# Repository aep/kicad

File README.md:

my personal collection of kicad components.
Some are not verified.

consider the ones i made public domain.

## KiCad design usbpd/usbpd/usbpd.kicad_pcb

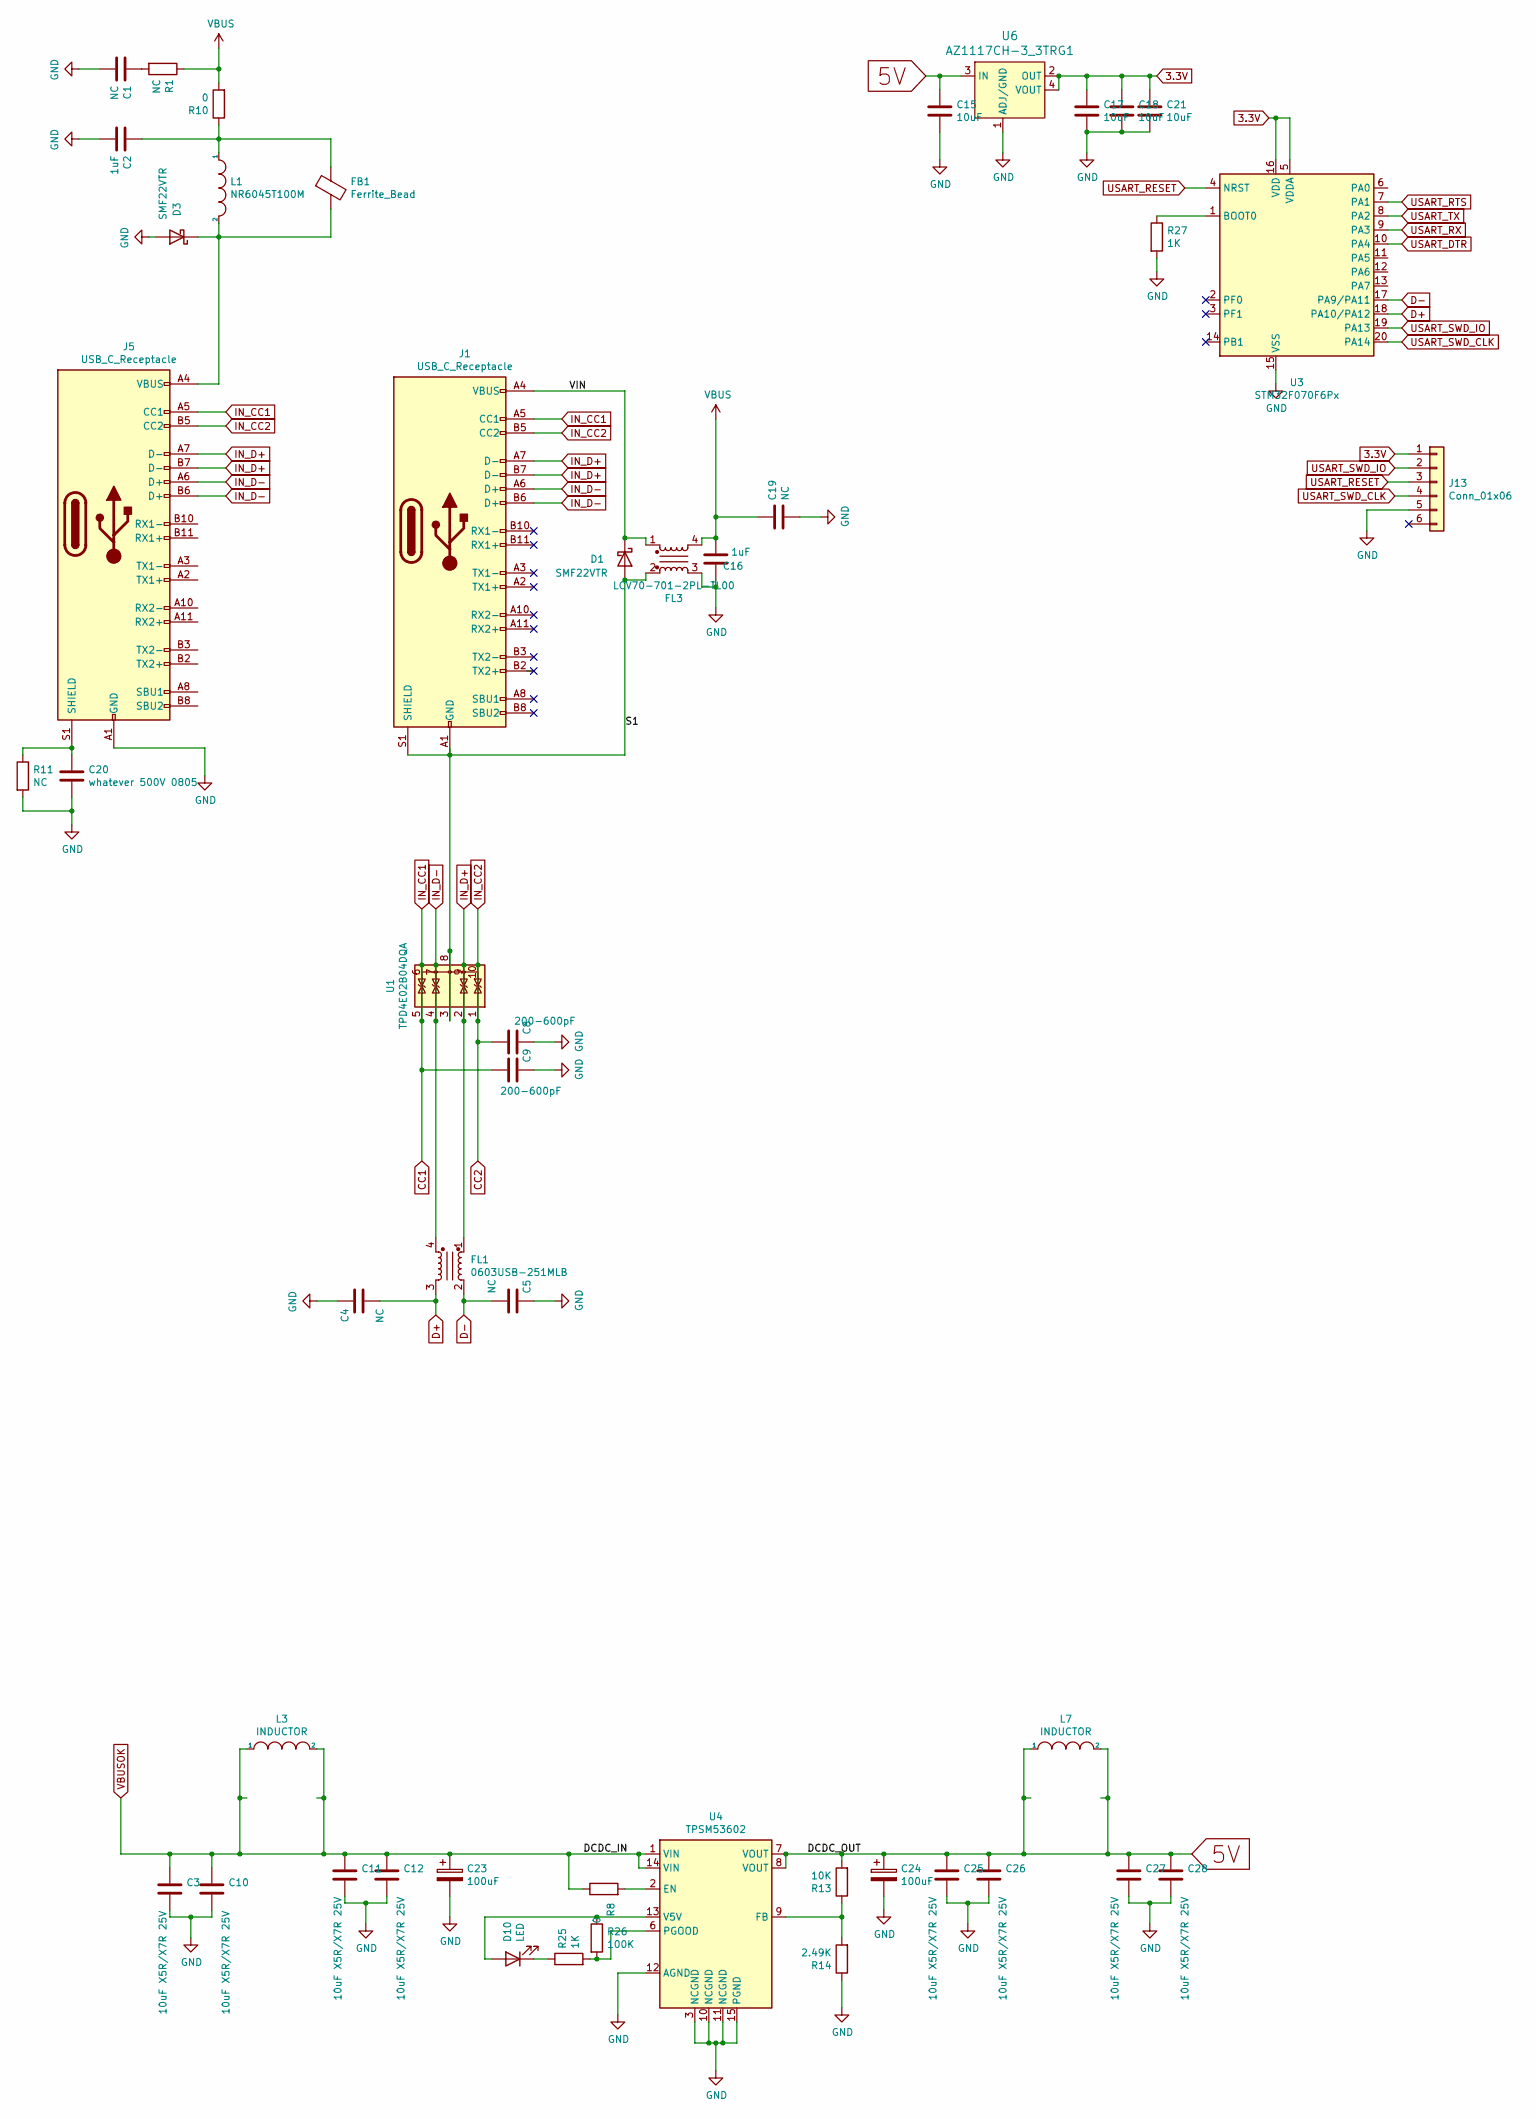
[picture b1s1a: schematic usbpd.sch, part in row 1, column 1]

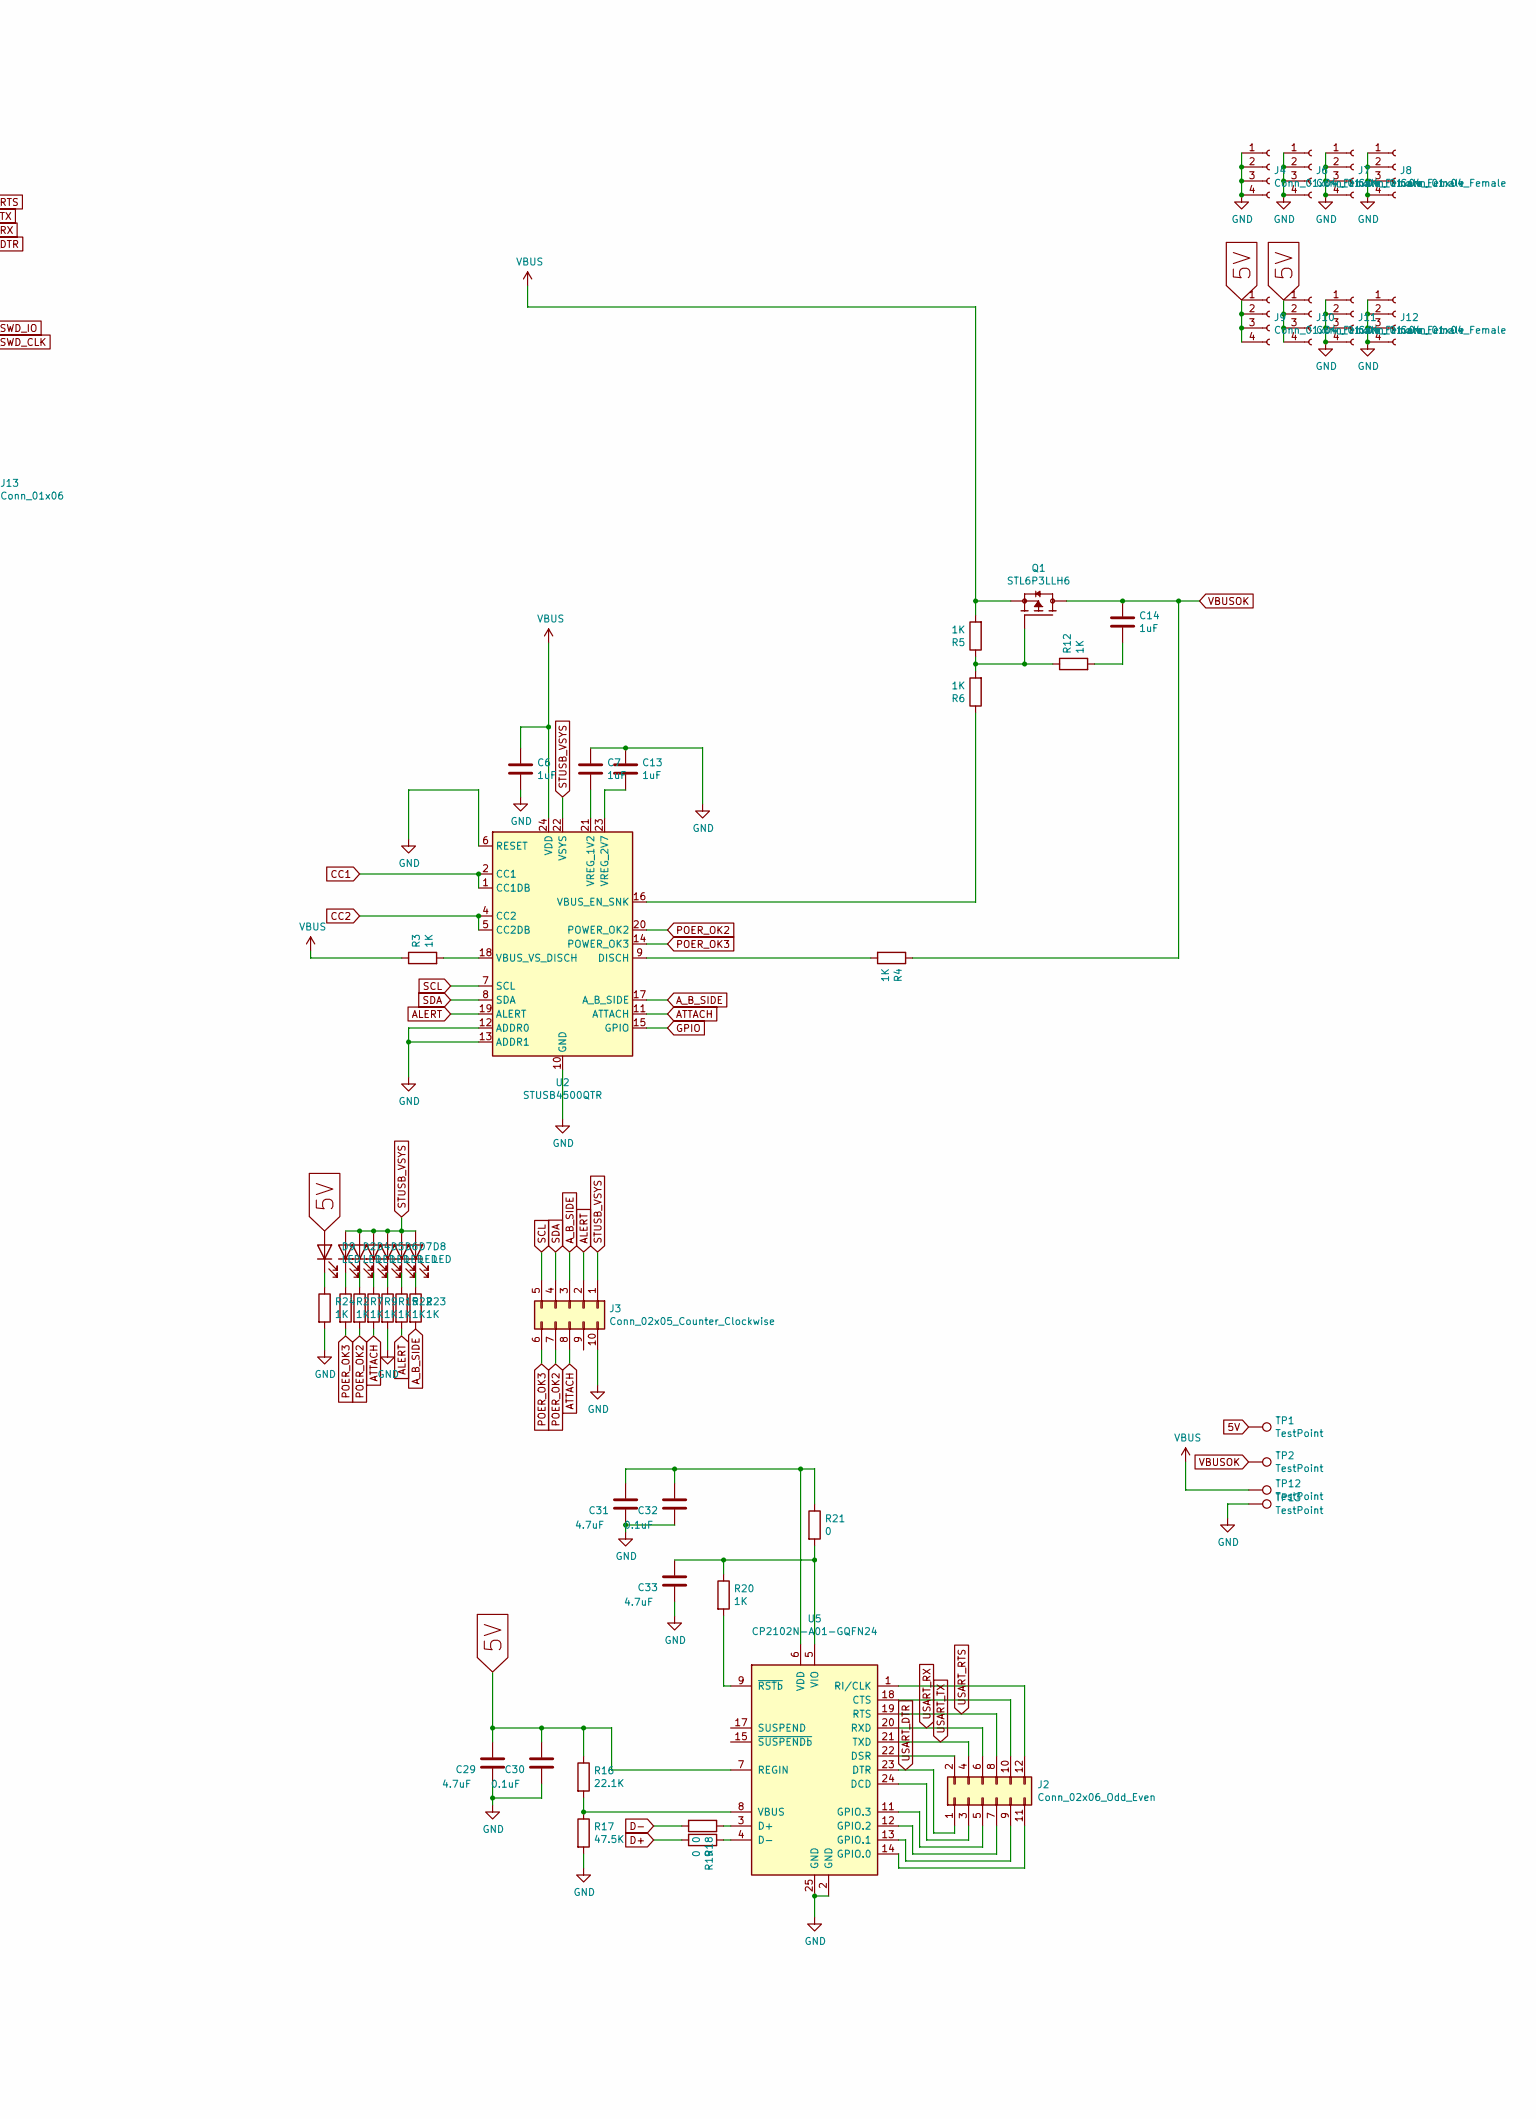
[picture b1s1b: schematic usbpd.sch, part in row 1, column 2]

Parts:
C1, C4, C5, C19: NC; C_0603_1608Metric
C2, C6, C7, C13, C14, C16: 1uF; C_0603_1608Metric
C3, C10, C11, C12, C25, C26, C27, C28: 10uF X5R/X7R 25V; C_0603_1608Metric
C8, C9: 200-600pF; C_0603_1608Metric
C15, C17, C18, C21: 10uF; C_0603_1608Metric
C20: whatever 500V 0805; C_0805_2012Metric
C23, C24: 100uF; C_Elec_8x10.2
C29, C31, C33: 4.7uF; C_0603_1608Metric
C30, C32: 0.1uF; C_0603_1608Metric
D1, D3: SMF22VTR; D_SOD-123F
D2, D4, D5, D6, D7, D8, D9, D10: LED; LED_0603
FB1: Ferrite_Bead; L_0805_2012Metric
FL1: 0603USB-251MLB; L_CommonModeChoke_Coilcraft_0603USB
FL3: LCV70-701-2PL-TL00; ACM70V
J1: USB_C_Receptacle; JAE_DX07B024JJ1R1500
J2: Conn_02x06_Odd_Even; PinHeader_2x06_P2.54mm_Vertical_SMD
J3: Conn_02x05_Counter_Clockwise; PinHeader_2x05_P2.54mm_Vertical_SMD
J4, J6, J7, J8, J9, J10, J11, J12: Conn_01x04_Female; Castellated_Edge_1x4_P2.54mm
J5: USB_C_Receptacle; USB-C-DX07S
J13: Conn_01x06; Tag-Connect_TC2030-IDC-FP_2x03_P1.27mm_Vertical
L1: NR6045T100M; L_Taiyo-Yuden_NR-60xx
L3, L7: INDUCTOR; L_1206_3216Metric
Q1: STL6P3LLH6; TRANS_STL6P3LLH6
R1, R11: NC; R_0603_1608Metric
R2, R3, R4, R5, R6, R7, R9, R12, R15, R20, R22, R23, R24, R25, R27: 1K; R_0603_1608Metric
R8, R10, R18, R19, R21: 0; R_0603_1608Metric
R13: 10K; R_0603_1608Metric
R14: 2.49K; R_0603_1608Metric
R16: 22.1K; R_0603_1608Metric
R17: 47.5K; R_0603_1608Metric
R26: 100K; R_0603_1608Metric
TP1, TP2, TP12, TP13: TestPoint; Test-Point-Pin_Drill2.79mm
U1: TPD4E02B04DQA; USON-10_2.5x1.0mm_P0.5mm_HAXED_MIDDLE
U2: STUSB4500QTR; QFN-24-1EP_4x4mm_P0.5mm_EP2.7x2.7mm
U3: STM32F070F6Px; TSSOP-20_4.4x6.5mm_P0.65mm
U4: TPSM53602; B3QFN
U5: CP2102N-A01-GQFN24; QFN-24-1EP_4x4mm_P0.5mm_EP2.6x2.6mm
U6: AZ1117CH-3_3TRG1; SOT-223; MPN AZ1117CH-3.3TRG1; Digi-Key_PN AZ1117CH-3.3TRG1DICT-ND

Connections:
3.3V: C17.1, C18.1, C21.1, J13.1, U3.5 (VDDA), U3.16 (VDD), U6.2 (OUT), U6.4 (VOUT)
5V: C15.1, C24.1, C25.1, C26.1, C27.1, C28.1, C29.2, C30.2, D9.2 (A), J9.1, J9.2, J9.3, J9.4, J10.1, J10.2, J10.3, J10.4, L7.1, L7.2, R13.2, R16.1, TP1.1, U4.7 (VOUT), U4.8 (VOUT), U5.7 (REGIN), U6.3 (IN)
/S1: D1.2 (A), FL3.2, J1.A1 (GND), J1.A12 (GND), J1.B1 (GND), J1.B12 (GND), J1.S1 (SHIELD), U1.3 (G), U1.8 (G)
/VIN: D1.1 (K), FL3.1, J1.A4 (VBUS), J1.A9 (VBUS), J1.B4 (VBUS), J1.B9 (VBUS)
ALERT: J3.2, R22.2, U2.19 (ALERT)
ATTACH: J3.8, R9.2, U2.11 (ATTACH)
A_B_SIDE: J3.3, R23.2, U2.17 (A_B_SIDE)
CC1: C9.1, J1.A5 (CC1), J5.A5 (CC1), U1.5 (IO4), U1.6 (NC), U2.1 (CC1DB), U2.2 (CC1)
CC2: C8.1, J1.B5 (CC2), J5.B5 (CC2), U1.1 (IO1), U1.10 (NC), U2.4 (CC2), U2.5 (CC2DB)
D+: C4.1, FL1.3, R19.2, U3.18 (PA10/PA12)
D-: C5.1, FL1.2, R18.2, U3.17 (PA9/PA11)
GND: C1.2, C2.2, C3.2, C4.2, C5.2, C6.2, C7.1, C8.2, C9.2, C10.2, C11.2, C12.2, C13.1, C15.2, C16.1, C17.2, C18.2, C19.2, C20.2, C21.2, C23.2, C24.2, C25.2, C26.2, C27.2, C28.2, C29.1, C30.1, C31.1, C32.1, C33.1, D3.2 (A), FL3.3, J3.10, J4.1, J4.2, J4.3, J4.4, J5.A1 (GND), J5.A12 (GND), J5.B1 (GND), J5.B12 (GND), J6.1, J6.2, J6.3, J6.4, J7.1, J7.2, J7.3, J7.4, J8.1, J8.2, J8.3, J8.4, J11.1, J11.2, J11.3, J11.4, J12.1, J12.2, J12.3, J12.4, J13.5, R11.2, R14.1, R15.2, R17.2, R24.2, R27.2, TP13.1, U2.6 (RESET), U2.10 (GND), U2.12 (ADDR0), U2.13 (ADDR1), U2.25 (GND), U3.15 (VSS), U4.3 (NCGND), U4.10 (NCGND), U4.11 (NCGND), U4.12 (AGND), U4.15 (PGND), U5.2 (GND), U5.25 (GND), U6.1 (ADJ/GND)
IN_D+: FL1.1, J1.A7 (D-), J1.B7 (D-), J5.A7 (D-), J5.B7 (D-), U1.2 (IO2), U1.9 (NC)
IN_D-: FL1.4, J1.A6 (D+), J1.B6 (D+), J5.A6 (D+), J5.B6 (D+), U1.4 (IO3), U1.7 (NC)
unnamed: C1.1, R1.2
unnamed: C2.1, FB1.1, L1.1, R10.1
unnamed: C7.2, U2.21 (VREG_1V2)
unnamed: C13.2, U2.23 (VREG_2V7)
unnamed: C14.2, R12.2
unnamed: C20.1, J5.S1 (SHIELD), R11.1
unnamed: C31.2, C32.2, R21.1, U5.6 (VDD)
unnamed: C33.2, R20.1, R21.2, U5.5 (VIO)
unnamed: D2.1 (K), R2.1
unnamed: D3.1 (K), FB1.2, J5.A4 (VBUS), J5.A9 (VBUS), J5.B4 (VBUS), J5.B9 (VBUS), L1.2
unnamed: D4.1 (K), R7.1
unnamed: D5.1 (K), R9.1
unnamed: D6.1 (K), R15.1
unnamed: D7.1 (K), R22.1
unnamed: D8.1 (K), R23.1
unnamed: D9.1 (K), R24.1
unnamed: D10.1 (K), R25.1
unnamed: D10.2 (A), R26.1, U4.13 (V5V)
unnamed: J2.2, U5.22 (DSR)
unnamed: J2.3, U5.24 (DCD)
unnamed: J2.5, U5.11 (GPIO.3)
unnamed: J2.7, U5.12 (GPIO.2)
unnamed: J2.9, U5.13 (GPIO.1)
unnamed: J2.10, U5.18 (CTS)
unnamed: J2.11, U5.14 (GPIO.0)
unnamed: J2.12, U5.1 (RI/CLK)
unnamed: Q1.4 (G), R5.1, R6.2, R12.1
unnamed: R3.2, U2.18 (VBUS_VS_DISCH)
unnamed: R4.2, U2.9 (DISCH)
unnamed: R6.1, U2.16 (VBUS_EN_SNK)
unnamed: R8.2, U4.2 (EN)
unnamed: R13.1, R14.2, U4.9 (FB)
unnamed: R16.2, R17.1, U5.8 (VBUS)
unnamed: R18.1, U5.3 (D+)
unnamed: R19.1, U5.4 (D-)
unnamed: R20.2, U5.9 (~RSTb)
unnamed: R25.2, R26.2, U4.6 (PGOOD)
unnamed: R27.1, U3.1 (BOOT0)
POER_OK2: J3.7, R7.2, U2.20 (POWER_OK2)
POER_OK3: J3.6, R2.2, U2.14 (POWER_OK3)
SCL: J3.5, U2.7 (SCL)
SDA: J3.4, U2.8 (SDA)
STUSB_VSYS: D2.2 (A), D4.2 (A), D5.2 (A), D6.2 (A), D7.2 (A), D8.2 (A), J3.1, U2.22 (VSYS)
USART_DTR: J2.1, U3.10 (PA4), U5.23 (DTR)
USART_RESET: J13.3, U3.4 (NRST)
USART_RTS: J2.8, U3.7 (PA1), U5.19 (RTS)
USART_RX: J2.6, U3.9 (PA3), U5.20 (RXD)
USART_SWD_CLK: J13.4, U3.20 (PA14)
USART_SWD_IO: J13.2, U3.19 (PA13)
USART_TX: J2.4, U3.8 (PA2), U5.21 (TXD)
VBUS: C6.1, C16.2, C19.1, FL3.4, Q1.1 (S), Q1.2 (S), Q1.3 (S), R1.1, R3.1, R5.2, R10.2, TP12.1, U2.24 (VDD)
VBUSOK: C3.1, C10.1, C11.1, C12.1, C14.1, C23.1, L3.1, L3.2, Q1.5_6_7_8 (D), R4.1, R8.1, TP2.1, U4.1 (VIN), U4.14 (VIN)

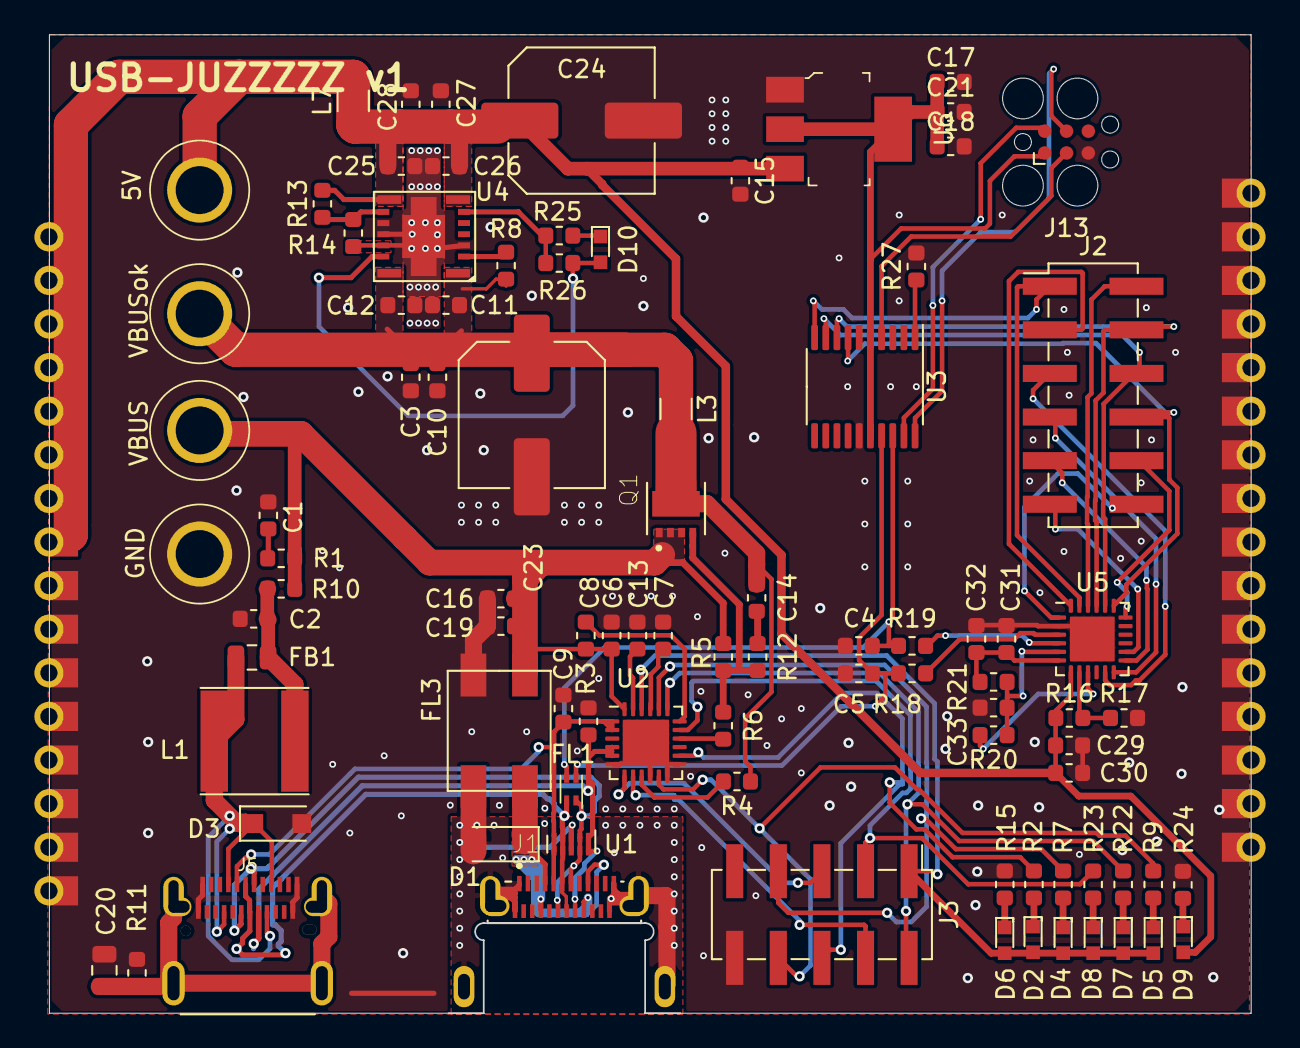
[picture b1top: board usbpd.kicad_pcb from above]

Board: 2 copper layers, 70.0 x 57.0 mm, 99 parts (0 on the bottom side), 66 nets.
